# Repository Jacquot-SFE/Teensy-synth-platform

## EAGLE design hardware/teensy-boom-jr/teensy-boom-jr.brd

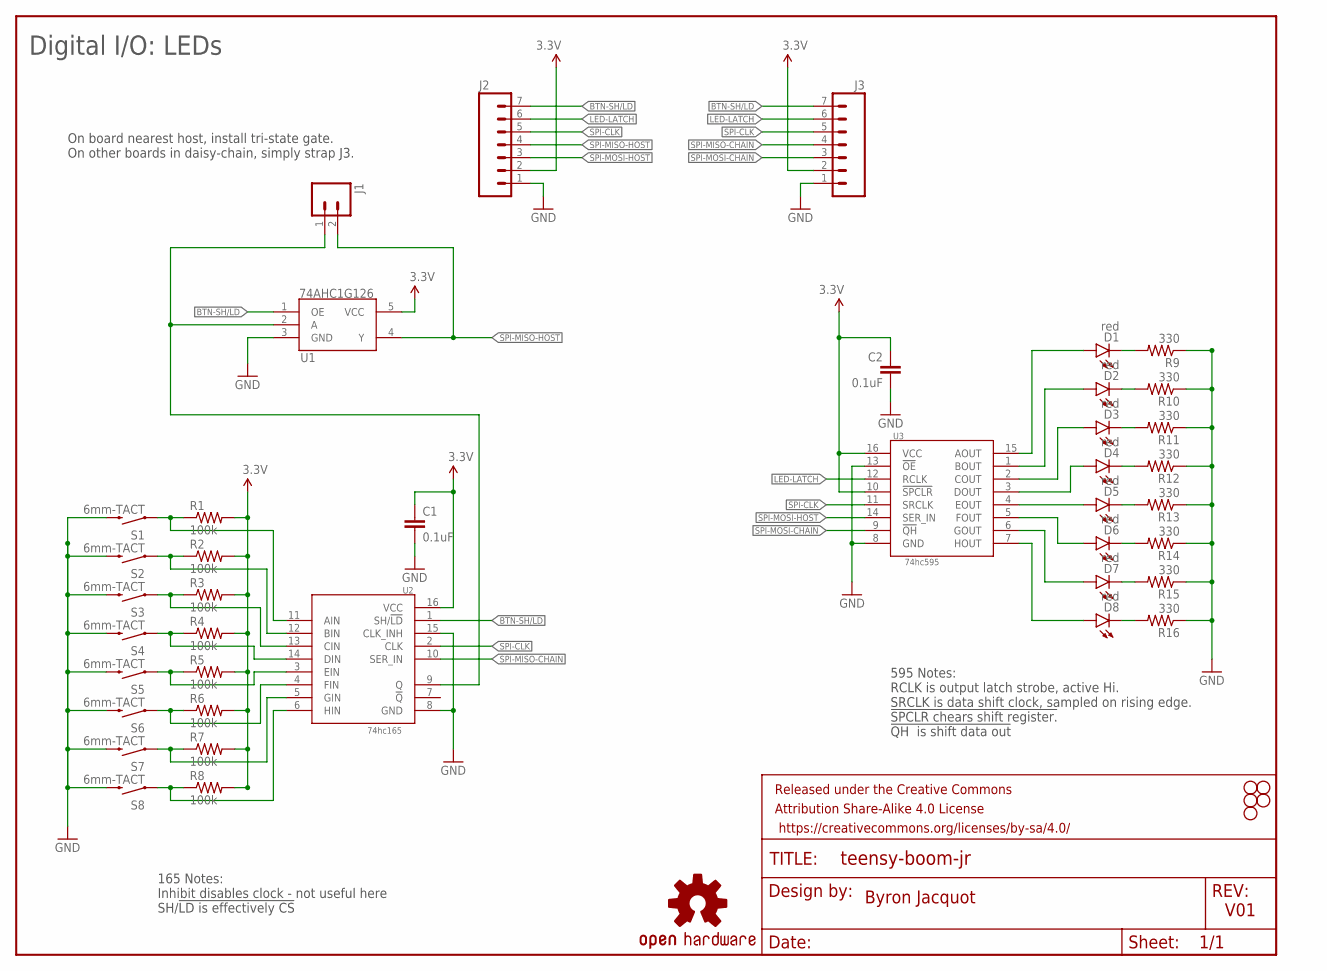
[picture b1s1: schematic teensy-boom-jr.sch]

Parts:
C1, C2: 0.1uF; 0603-CAP
D1, D2, D3, D4, D5, D6, D7, D8: red; LED3MM-NS
FRAME1: FRAME-LETTERNO_PACKAGE; DUMMY
H1, H2, H3, H4, H5: STAND-OFF
J1: M021X02_NO_SILK; 1X02_NO_SILK
J2, J3: M07NO_SILK; 1X07_NO_SILK
LOGO1: OSHW-LOGOS; OSHW-LOGO-S
R1, R2, R3, R4, R5, R6, R7, R8: 100k; 0805
R9, R10, R11, R12, R13, R14, R15, R16: 330; 0603-RES
S1, S2, S3, S4, S5, S6, S7, S8: 6mm-TACT; TACTILE-PTH-12MM
U1: 74AHC1G126; SOT23-5
U2: 74hc165; SO16
U3: 74hc595; SO16

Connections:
3.3V: C1.1, C2.1, J2.2, J3.2, R1.2, R2.2, R3.2, R4.2, R5.2, R6.2, R7.2, R8.2, U1.5 (VCC), U2.16 (VCC), U3.10 (!SPCLR), U3.16 (VCC)
BTN-SH/LD: J2.7, J3.7, U1.1 (OE), U2.1 (SH/!LD)
GND: C1.2, C2.2, J2.1, J3.1, R9.1, R10.1, R11.1, R12.1, R13.1, R14.1, R15.1, R16.1, S1.3 (2), S2.3 (2), S3.3 (2), S4.3 (2), S5.3 (2), S6.3 (2), S7.3 (2), S8.3 (2), U1.3 (GND), U2.8 (GND), U2.15 (CLK_INH), U3.8 (GND), U3.13 (!OE)
LED-LATCH: J2.6, J3.6, U3.12 (RCLK)
unnamed: R1.1, S1.1, U2.11 (AIN)
unnamed: R2.1, S2.1, U2.12 (BIN)
unnamed: R3.1, S3.1, U2.13 (CIN)
unnamed: R4.1, S4.1, U2.14 (DIN)
unnamed: D8.K (C), R16.2
unnamed: R5.1, S5.1, U2.3 (EIN)
unnamed: R6.1, S6.1, U2.4 (FIN)
unnamed: R7.1, S7.1, U2.5 (GIN)
unnamed: D7.K (C), R15.2
unnamed: D6.K (C), R14.2
unnamed: D5.K (C), R13.2
unnamed: D4.K (C), R12.2
unnamed: D3.K (C), R11.2
unnamed: D2.K (C), R10.2
unnamed: D1.K (C), R9.2
unnamed: R8.1, S8.1, U2.6 (HIN)
unnamed: J1.1, U1.2 (A), U2.9 (Q)
unnamed: D4.A, U3.3 (DOUT)
unnamed: D5.A, U3.4 (EOUT)
unnamed: D6.A, U3.5 (FOUT)
unnamed: D7.A, U3.6 (GOUT)
unnamed: D8.A, U3.7 (HOUT)
unnamed: D3.A, U3.2 (COUT)
unnamed: D2.A, U3.1 (BOUT)
unnamed: D1.A, U3.15 (AOUT)
SPI-CLK: J2.5, J3.5, U2.2 (CLK), U3.11 (SRCLK)
SPI-MISO-CHAIN: J3.4, U2.10 (SER_IN)
SPI-MISO-HOST: J1.2, J2.4, U1.4 (Y)
SPI-MOSI-CHAIN: J3.3, U3.9 (!QH)
SPI-MOSI-HOST: J2.3, U3.14 (SER_IN)

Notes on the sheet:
Digital I/O: LEDs
595 Notes: RCLK is output latch strobe, active Hi. SRCLK is data shift clock, sampled on rising edge. !SPCLR chears shift register. !QH is shift data out
On board nearest host, install tri-state gate. On other boards in daisy-chain, simply strap J3.
165 Notes: Inhibit disables clock - not useful here SH/!LD is effectively CS
Byron Jacquot
V01

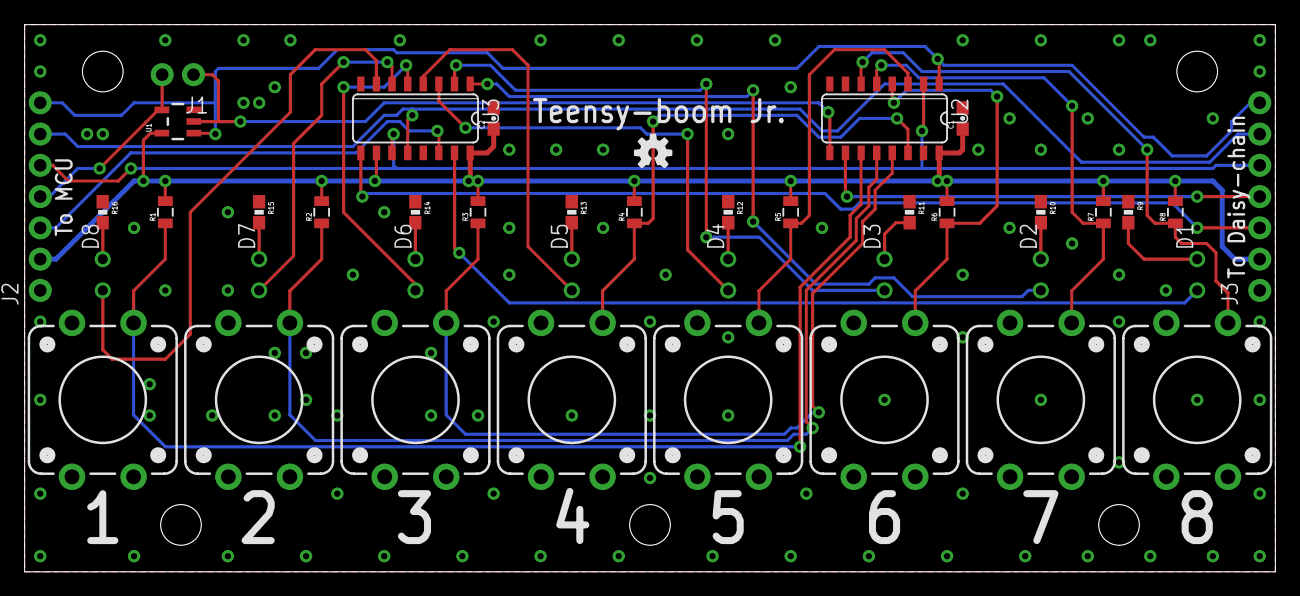
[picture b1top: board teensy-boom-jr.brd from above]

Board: 2 copper layers, 101.6 x 44.5 mm, 47 parts (0 on the bottom side), 34 nets.

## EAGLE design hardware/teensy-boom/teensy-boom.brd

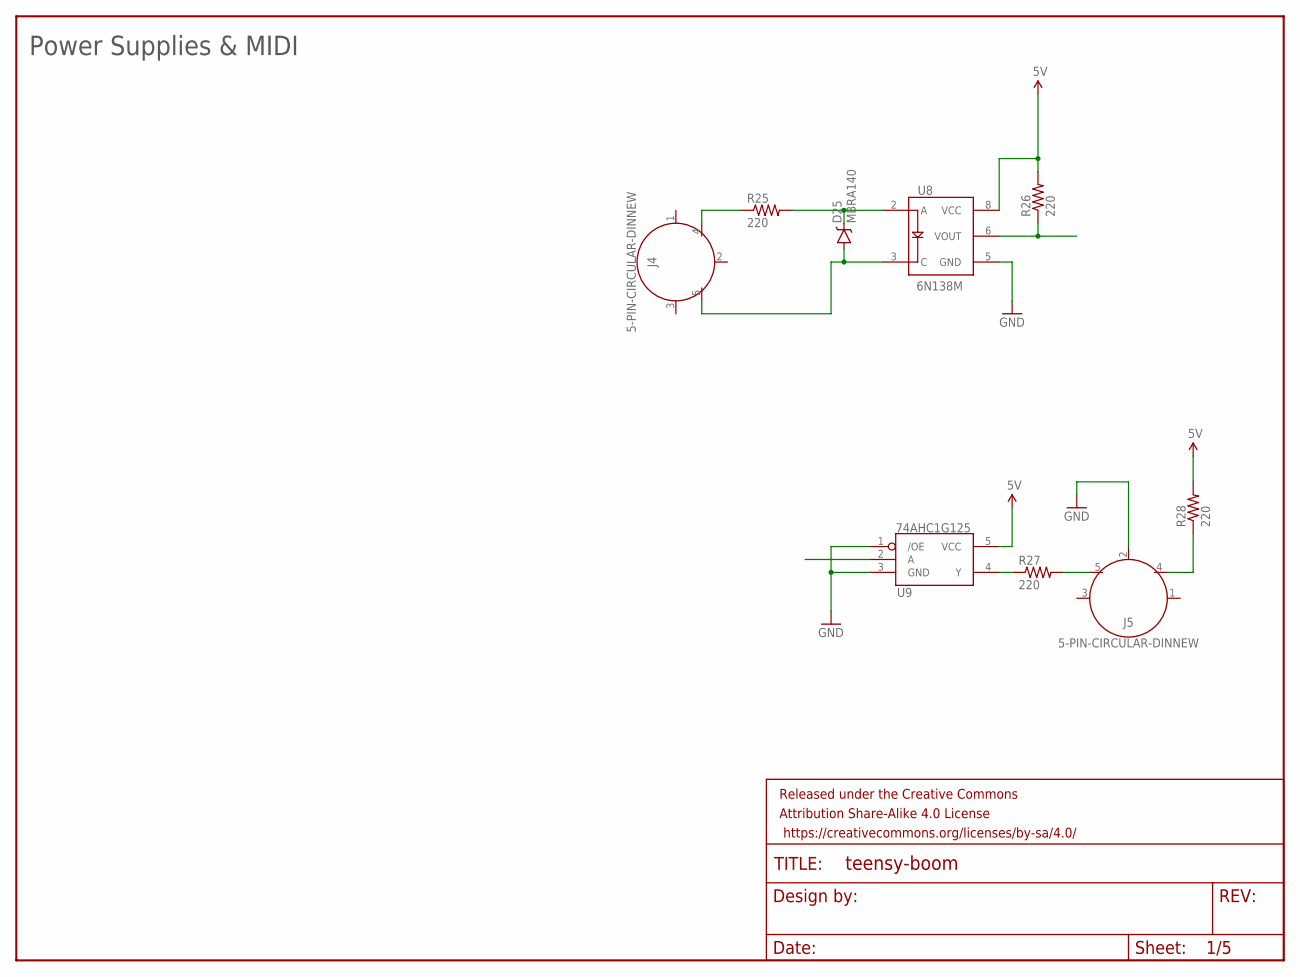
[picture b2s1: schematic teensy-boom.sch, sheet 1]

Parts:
D25: MBRA140; SMA-DIODE
FRAME2: FRAME-LETTERNO_PACKAGE; DUMMY
J4, J5: 5-PIN-CIRCULAR-DINNEW; 5-PIN-DIN-RA-PCB-NEW
R25, R26, R27, R28: 220; 0603-RES
U8: 6N138M; 8-SMD
U9: 74AHC1G125; SOT23-5

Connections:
5V: R26.2, R28.2, U8.8 (VCC), U9.5 (VCC)
GND: J5.2, U8.5 (GND), U9.1 (/OE), U9.3 (GND); also elsewhere on the board
unnamed: J4.4, R25.1
unnamed: D25.C, R25.2, U8.2 (A)
unnamed: D25.A, J4.5, U8.3 (C)
unnamed: R26.1, U8.6 (VOUT)
unnamed: R27.1, U9.4 (Y)
unnamed: J5.5, R27.2
unnamed: J5.4, R28.1

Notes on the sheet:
Power Supplies & MIDI

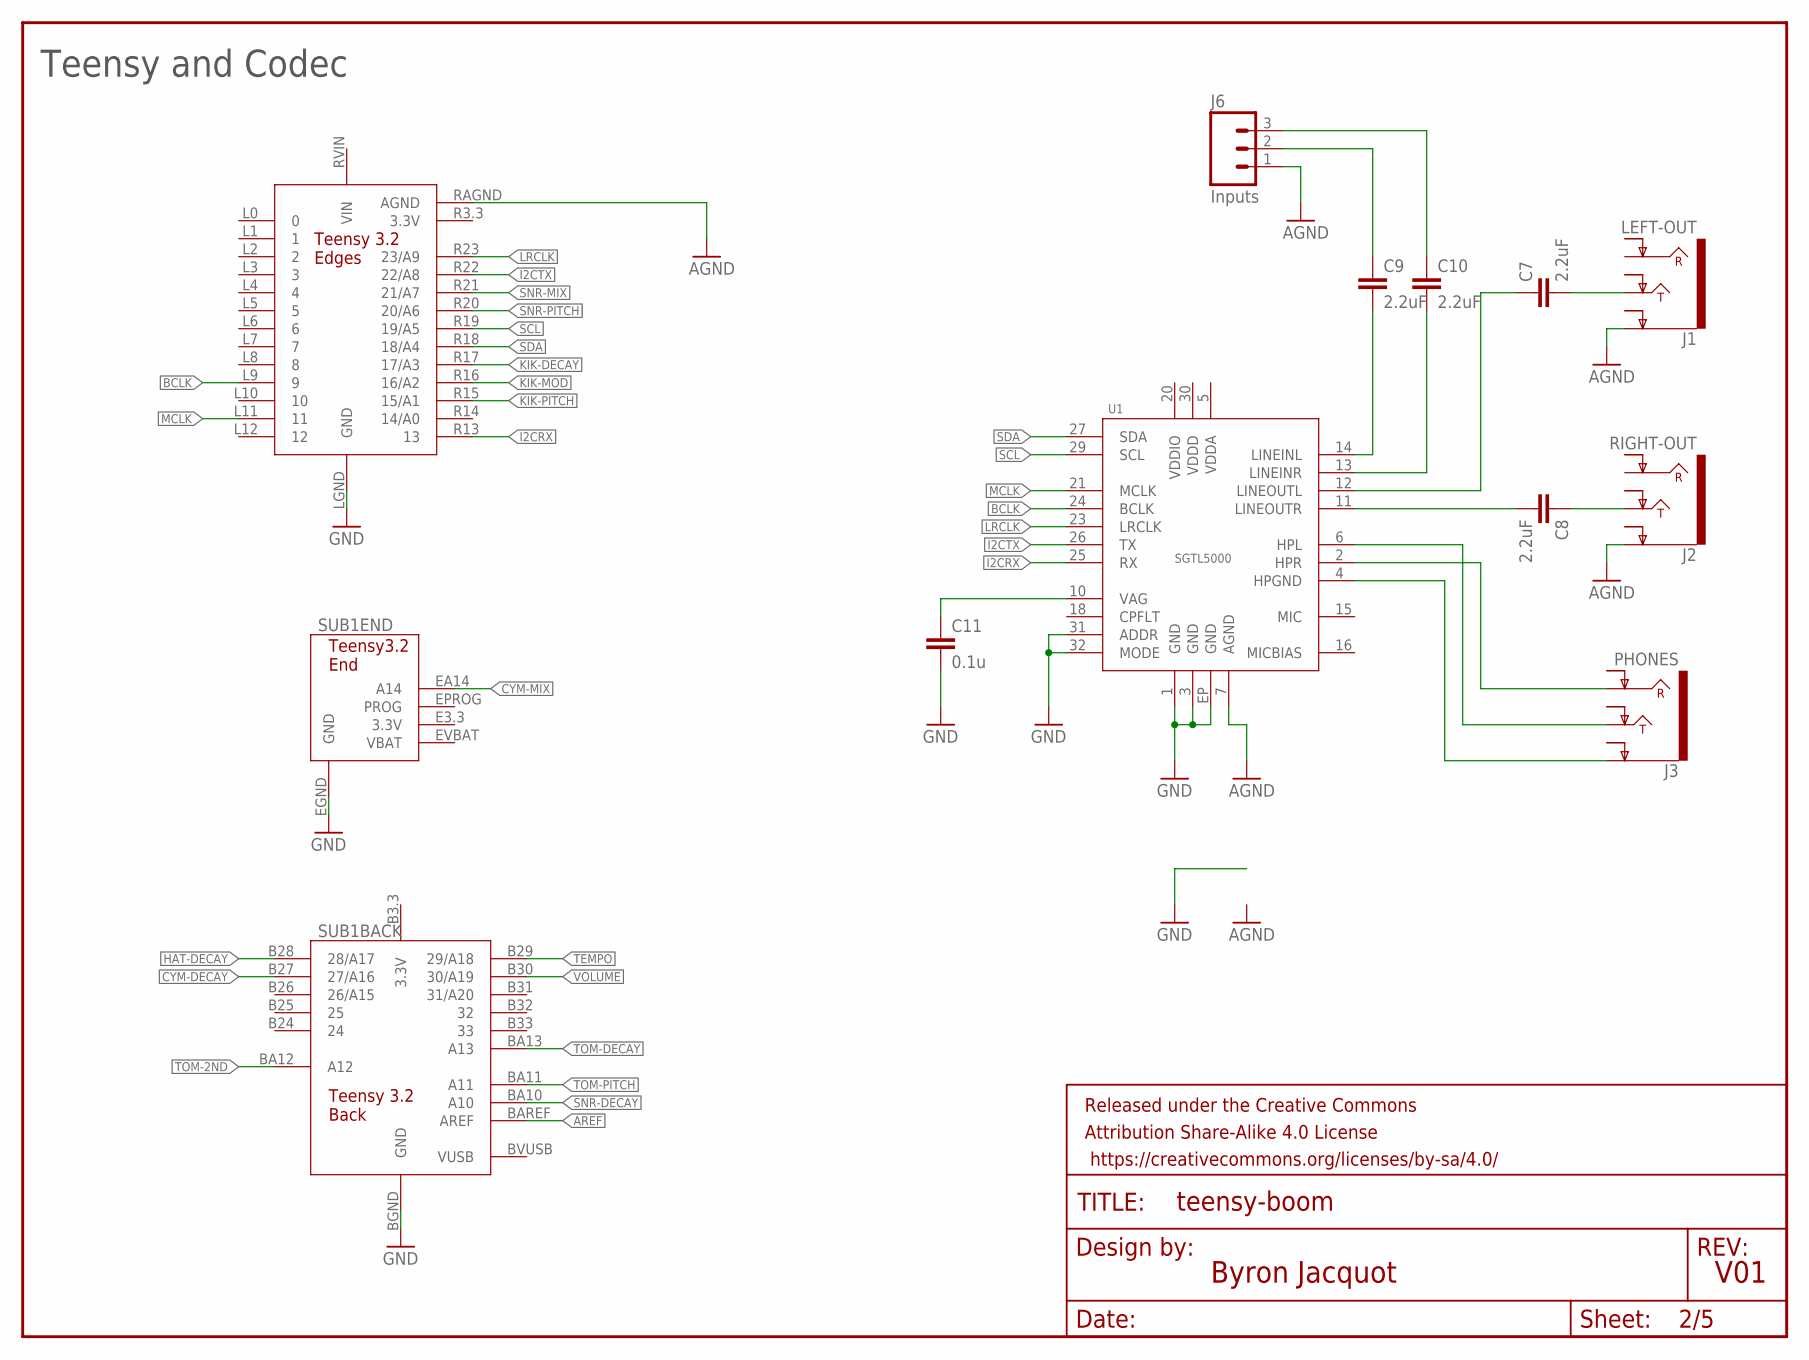
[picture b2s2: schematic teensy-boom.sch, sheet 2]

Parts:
C7, C8, C9, C10: 2.2uF; 0805-CAP
C11: 0.1u; 0805
FRAME1: FRAME-LETTER; CREATIVE_COMMONS
J1: LEFT-OUT; AUDIO-JACK-.25-INCH-HORIZ-PTH
J2: RIGHT-OUT; AUDIO-JACK-.25-INCH-HORIZ-PTH
J3: PHONES; AUDIO-JACK-.25-INCH-HORIZ-PTH
J6: Inputs; 1X03_LOCK
SUB1: TEENSY-3.2PTH; TEENSY-3.2
U1: SGTL5000; QFN-32

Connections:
AGND: J1.SLEEVE (EARTH), J2.SLEEVE (EARTH), J6.1, SUB1.RAGND (AGND), U1.7 (AGND); also elsewhere on the board
AREF: SUB1.BAREF (AREF); also elsewhere on the board
BCLK: SUB1.L9 (9), U1.24 (BCLK)
CYM-DECAY: SUB1.B27 (27/A16); also elsewhere on the board
CYM-MIX: SUB1.EA14 (A14); also elsewhere on the board
GND: C11.2, SUB1.BGND (GND), SUB1.EGND (GND), SUB1.LGND (GND), U1.1 (GND), U1.3 (GND), U1.31 (ADDR), U1.32 (MODE), U1.EP (GND); also elsewhere on the board
HAT-DECAY: SUB1.B28 (28/A17); also elsewhere on the board
I2CRX: SUB1.R13 (13), U1.25 (RX)
I2CTX: SUB1.R22 (22/A8), U1.26 (TX)
KIK-DECAY: SUB1.R17 (17/A3); also elsewhere on the board
KIK-MOD: SUB1.R16 (16/A2); also elsewhere on the board
KIK-PITCH: SUB1.R15 (15/A1); also elsewhere on the board
LRCLK: SUB1.R23 (23/A9), U1.23 (LRCLK)
MCLK: SUB1.L11 (11), U1.21 (MCLK)
unnamed: C8.1, J2.TIP
unnamed: C7.2, J1.TIP
unnamed: C8.2, U1.11 (LINEOUTR)
unnamed: C7.1, U1.12 (LINEOUTL)
unnamed: C10.2, U1.13 (LINEINR)
unnamed: C9.2, U1.14 (LINEINL)
unnamed: J3.TIP, U1.6 (HPL)
unnamed: J3.RING, U1.2 (HPR)
unnamed: J3.SLEEVE (EARTH), U1.4 (HPGND)
unnamed: C9.1, J6.2
unnamed: C10.1, J6.3
unnamed: C11.1, U1.10 (VAG)
SCL: SUB1.R19 (19/A5), U1.29 (SCL)
SDA: SUB1.R18 (18/A4), U1.27 (SDA)
SNR-DECAY: SUB1.BA10 (A10); also elsewhere on the board
SNR-MIX: SUB1.R21 (21/A7); also elsewhere on the board
SNR-PITCH: SUB1.R20 (20/A6); also elsewhere on the board
TEMPO: SUB1.B29 (29/A18); also elsewhere on the board
TOM-2ND: SUB1.BA12 (A12); also elsewhere on the board
TOM-DECAY: SUB1.BA13 (A13); also elsewhere on the board
TOM-PITCH: SUB1.BA11 (A11); also elsewhere on the board
VOLUME: SUB1.B30 (30/A19); also elsewhere on the board

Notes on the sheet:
V01
Byron Jacquot
Teensy and Codec

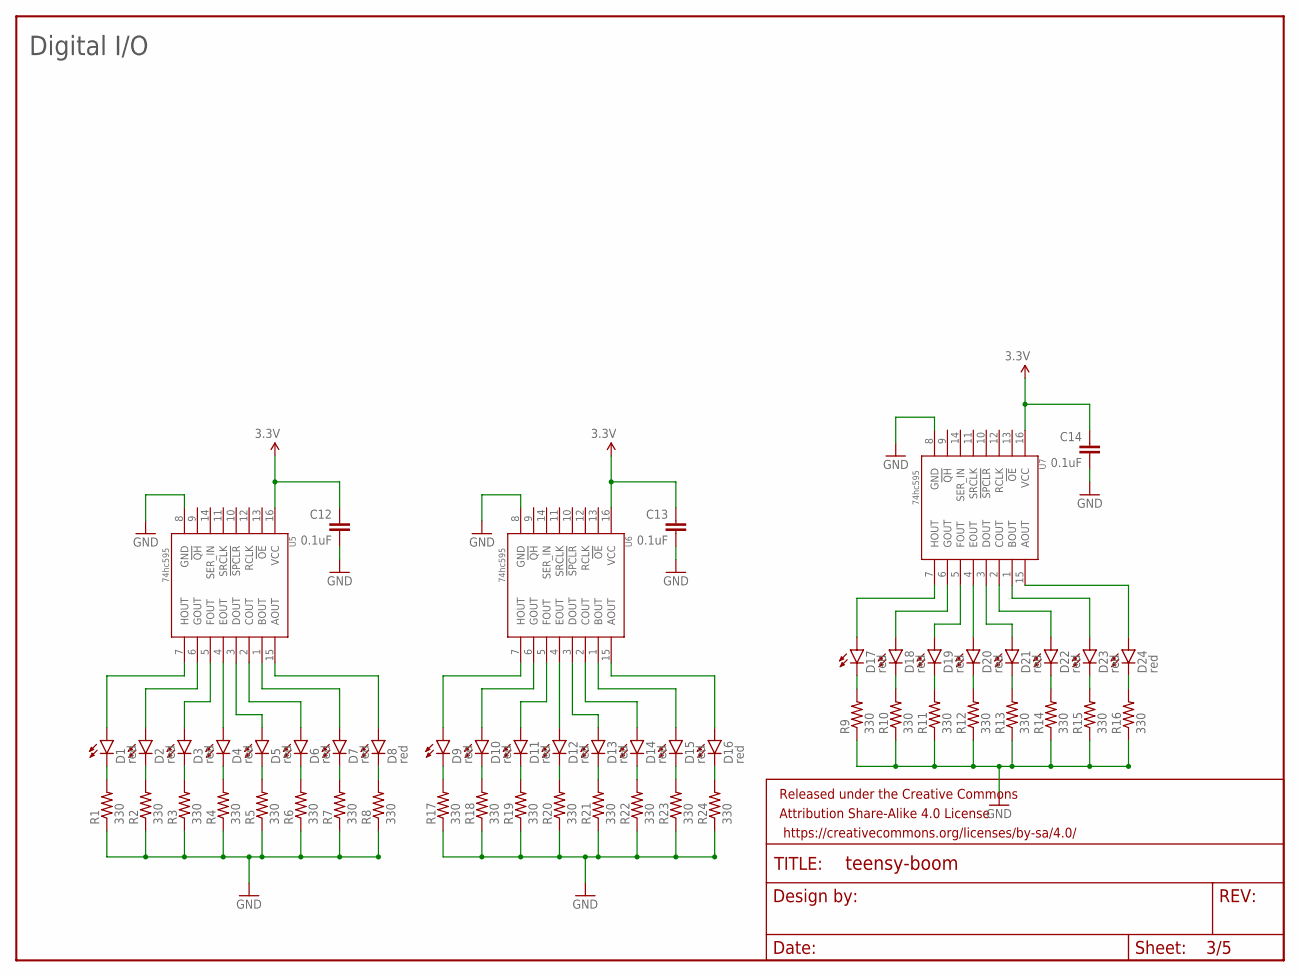
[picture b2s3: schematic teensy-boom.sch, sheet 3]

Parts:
C12, C13, C14: 0.1uF; 0603-CAP
D1, D2, D3, D4, D5, D6, D7, D8, D9, D10, D11, D12, D13, D14, D15, D16, D17, D18, D19, D20, D21, D22, D23, D24: red; LED3MM-NS
FRAME3: FRAME-LETTERNO_PACKAGE; DUMMY
R1, R2, R3, R4, R5, R6, R7, R8, R9, R10, R11, R12, R13, R14, R15, R16, R17, R18, R19, R20, R21, R22, R23, R24: 330; 0603-RES
U5, U6, U7: 74hc595; SO16

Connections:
3.3V: C12.1, C13.1, C14.1, U5.16 (VCC), U6.16 (VCC), U7.16 (VCC); also elsewhere on the board
GND: C12.2, C13.2, C14.2, R1.1, R2.1, R3.1, R4.1, R5.1, R6.1, R7.1, R8.1, R9.1, R10.1, R11.1, R12.1, R13.1, R14.1, R15.1, R16.1, R17.1, R18.1, R19.1, R20.1, R21.1, R22.1, R23.1, R24.1, U5.8 (GND), U6.8 (GND), U7.8 (GND); also elsewhere on the board
unnamed: D1.K (C), R1.2
unnamed: D2.K (C), R2.2
unnamed: D3.K (C), R3.2
unnamed: D4.K (C), R4.2
unnamed: D5.K (C), R5.2
unnamed: D6.K (C), R6.2
unnamed: D7.K (C), R7.2
unnamed: D8.K (C), R8.2
unnamed: D9.K (C), R17.2
unnamed: D10.K (C), R18.2
unnamed: D11.K (C), R19.2
unnamed: D12.K (C), R20.2
unnamed: D13.K (C), R21.2
unnamed: D14.K (C), R22.2
unnamed: D15.K (C), R23.2
unnamed: D16.K (C), R24.2
unnamed: D17.K (C), R9.2
unnamed: D18.K (C), R10.2
unnamed: D19.K (C), R11.2
unnamed: D20.K (C), R12.2
unnamed: D21.K (C), R13.2
unnamed: D22.K (C), R14.2
unnamed: D23.K (C), R15.2
unnamed: D24.K (C), R16.2
unnamed: D5.A, U5.3 (DOUT)
unnamed: D4.A, U5.4 (EOUT)
unnamed: D3.A, U5.5 (FOUT)
unnamed: D2.A, U5.6 (GOUT)
unnamed: D1.A, U5.7 (HOUT)
unnamed: D6.A, U5.2 (COUT)
unnamed: D7.A, U5.1 (BOUT)
unnamed: D8.A, U5.15 (AOUT)
unnamed: D12.A, U6.4 (EOUT)
unnamed: D11.A, U6.5 (FOUT)
unnamed: D10.A, U6.6 (GOUT)
unnamed: D9.A, U6.7 (HOUT)
unnamed: D13.A, U6.3 (DOUT)
unnamed: D14.A, U6.2 (COUT)
unnamed: D15.A, U6.1 (BOUT)
unnamed: D16.A, U6.15 (AOUT)
unnamed: D20.A, U7.4 (EOUT)
unnamed: D19.A, U7.5 (FOUT)
unnamed: D18.A, U7.6 (GOUT)
unnamed: D17.A, U7.7 (HOUT)
unnamed: D21.A, U7.3 (DOUT)
unnamed: D24.A, U7.15 (AOUT)
unnamed: D23.A, U7.1 (BOUT)
unnamed: D22.A, U7.2 (COUT)

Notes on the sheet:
Digital I/O

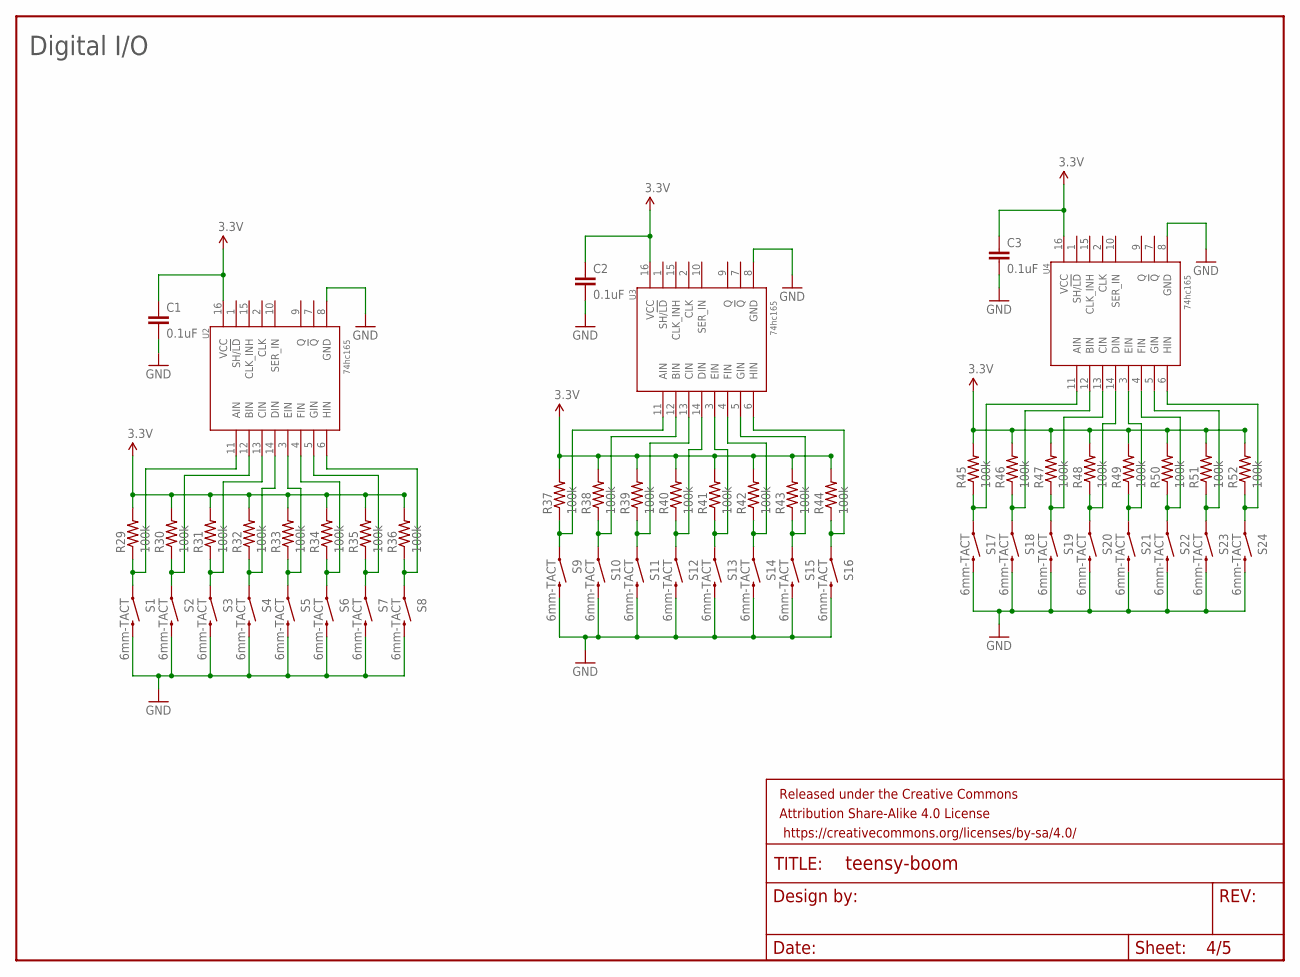
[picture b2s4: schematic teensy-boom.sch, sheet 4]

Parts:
C1, C2, C3: 0.1uF; 0603-CAP
FRAME5: FRAME-LETTERNO_PACKAGE; DUMMY
R29, R30, R31, R32, R33, R34, R35, R36, R37, R38, R39, R40, R41, R42, R43, R44, R45, R46, R47, R48, R49, R50, R51, R52: 100k; 0805
S1, S2, S3, S4, S5, S6, S7, S8, S9, S10, S11, S12, S13, S14, S15, S16, S17, S18, S19, S20, S21, S22, S23, S24: 6mm-TACT; TACTILE-PTH
U2, U3, U4: 74hc165; SO16

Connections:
3.3V: C1.1, C2.1, C3.1, R29.2, R30.2, R31.2, R32.2, R33.2, R34.2, R35.2, R36.2, R37.2, R38.2, R39.2, R40.2, R41.2, R42.2, R43.2, R44.2, R45.2, R46.2, R47.2, R48.2, R49.2, R50.2, R51.2, R52.2, U2.16 (VCC), U3.16 (VCC), U4.16 (VCC); also elsewhere on the board
GND: C1.2, C2.2, C3.2, S1.3 (2), S2.3 (2), S3.3 (2), S4.3 (2), S5.3 (2), S6.3 (2), S7.3 (2), S8.3 (2), S9.3 (2), S10.3 (2), S11.3 (2), S12.3 (2), S13.3 (2), S14.3 (2), S15.3 (2), S16.3 (2), S17.3 (2), S18.3 (2), S19.3 (2), S20.3 (2), S21.3 (2), S22.3 (2), S23.3 (2), S24.3 (2), U2.8 (GND), U3.8 (GND), U4.8 (GND); also elsewhere on the board
unnamed: R35.1, S7.1, U2.5 (GIN)
unnamed: R29.1, S1.1, U2.11 (AIN)
unnamed: R30.1, S2.1, U2.12 (BIN)
unnamed: R31.1, S3.1, U2.13 (CIN)
unnamed: R32.1, S4.1, U2.14 (DIN)
unnamed: R33.1, S5.1, U2.3 (EIN)
unnamed: R34.1, S6.1, U2.4 (FIN)
unnamed: R36.1, S8.1, U2.6 (HIN)
unnamed: R37.1, S9.1, U3.11 (AIN)
unnamed: R38.1, S10.1, U3.12 (BIN)
unnamed: R39.1, S11.1, U3.13 (CIN)
unnamed: R40.1, S12.1, U3.14 (DIN)
unnamed: R41.1, S13.1, U3.3 (EIN)
unnamed: R42.1, S14.1, U3.4 (FIN)
unnamed: R43.1, S15.1, U3.5 (GIN)
unnamed: R44.1, S16.1, U3.6 (HIN)
unnamed: R45.1, S17.1, U4.11 (AIN)
unnamed: R46.1, S18.1, U4.12 (BIN)
unnamed: R47.1, S19.1, U4.13 (CIN)
unnamed: R48.1, S20.1, U4.14 (DIN)
unnamed: R49.1, S21.1, U4.3 (EIN)
unnamed: R50.1, S22.1, U4.4 (FIN)
unnamed: R51.1, S23.1, U4.5 (GIN)
unnamed: R52.1, S24.1, U4.6 (HIN)

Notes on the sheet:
Digital I/O

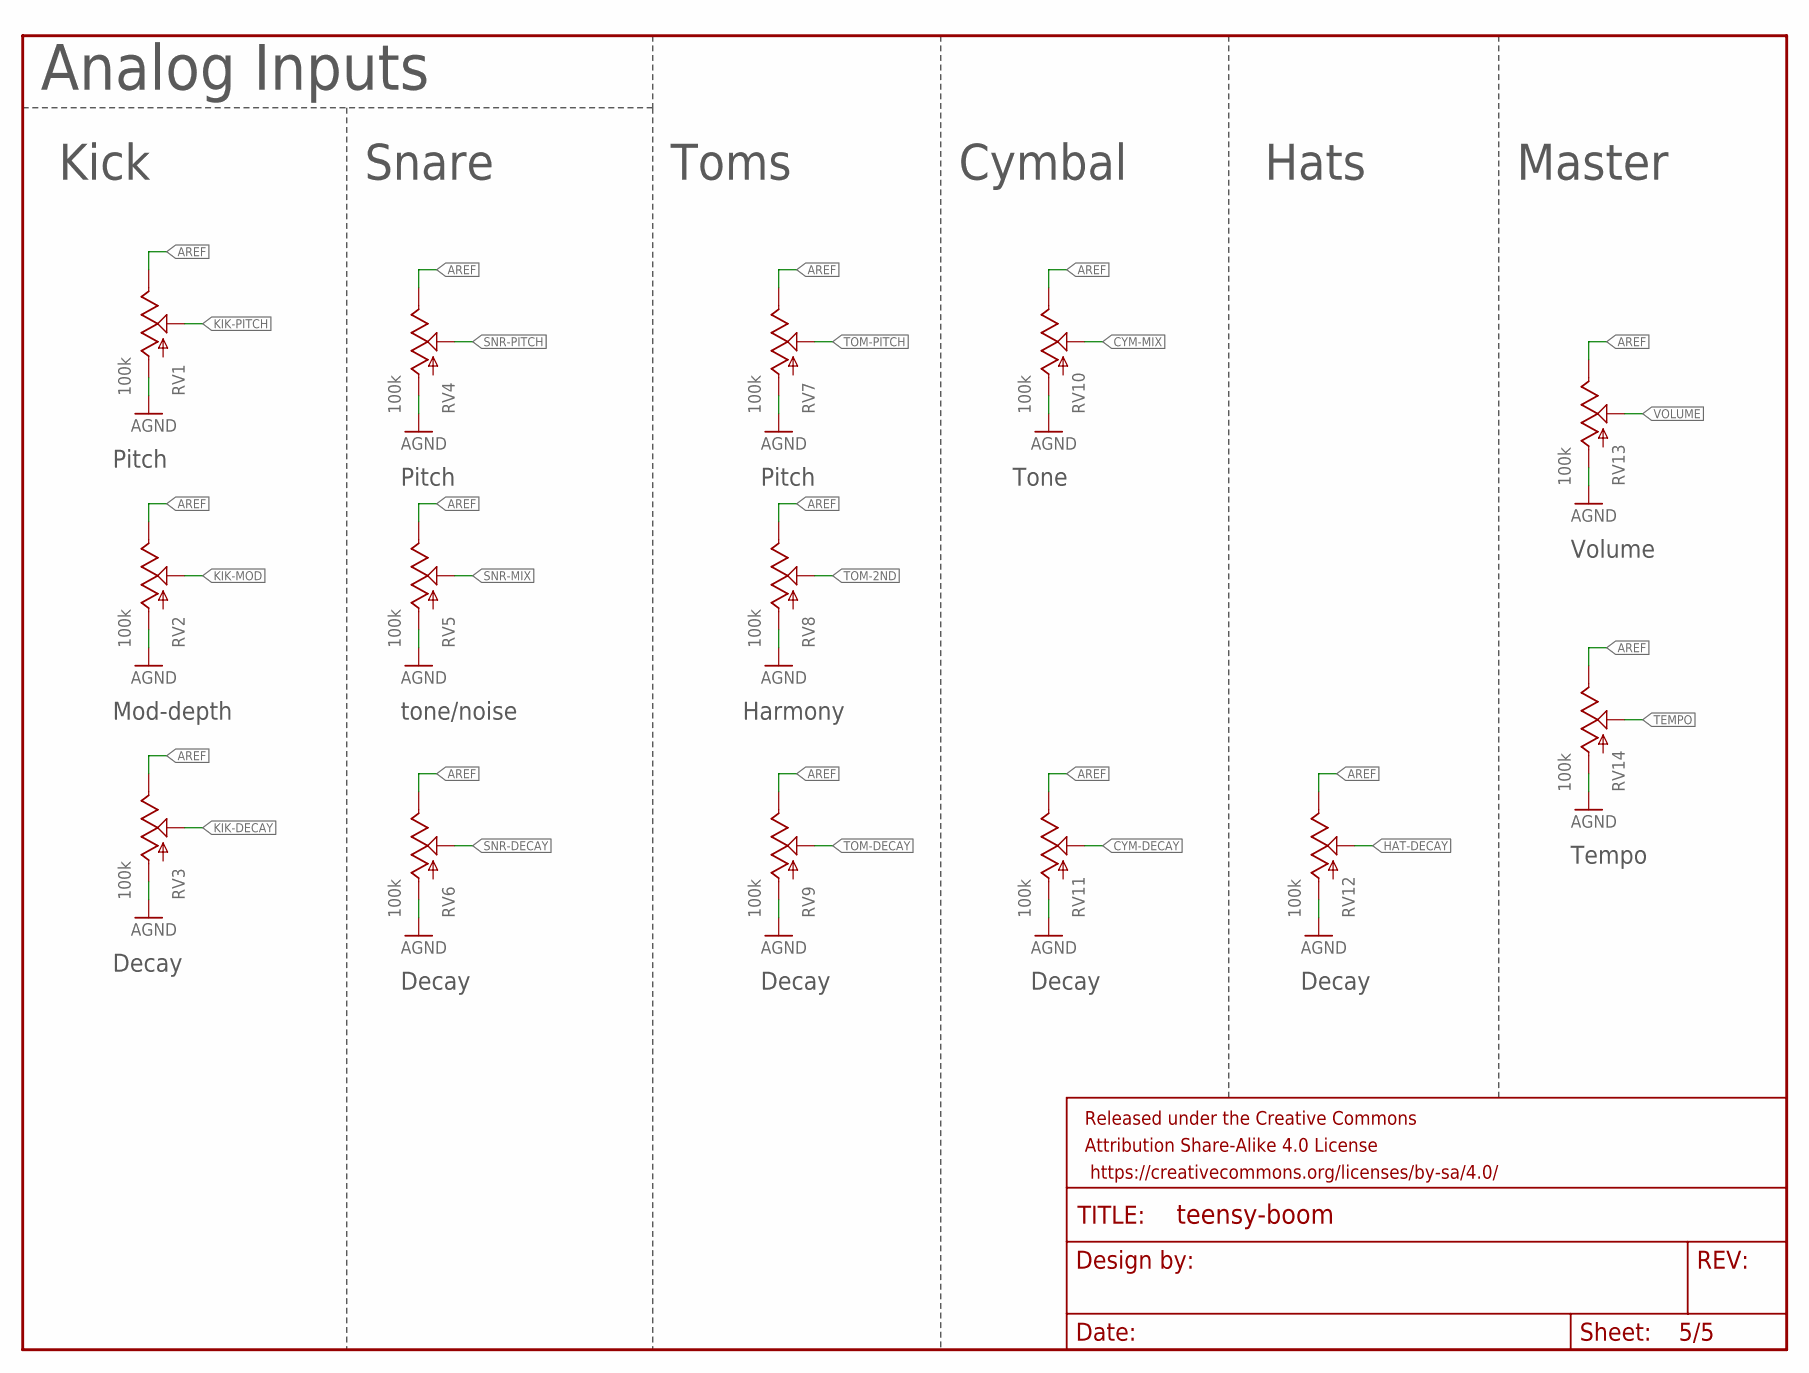
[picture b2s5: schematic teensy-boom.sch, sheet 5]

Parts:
FRAME4: FRAME-LETTERNO_PACKAGE; DUMMY
RV1, RV2, RV3, RV4, RV5, RV6, RV7, RV8, RV9, RV10, RV11, RV12, RV13, RV14: 100k; ALPS_POT_KIT

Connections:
AGND: RV1.P$3 (A), RV2.P$3 (A), RV3.P$3 (A), RV4.P$3 (A), RV5.P$3 (A), RV6.P$3 (A), RV7.P$3 (A), RV8.P$3 (A), RV9.P$3 (A), RV10.P$3 (A), RV11.P$3 (A), RV12.P$3 (A), RV13.P$3 (A), RV14.P$3 (A); also elsewhere on the board
AREF: RV1.P$1 (E), RV2.P$1 (E), RV3.P$1 (E), RV4.P$1 (E), RV5.P$1 (E), RV6.P$1 (E), RV7.P$1 (E), RV8.P$1 (E), RV9.P$1 (E), RV10.P$1 (E), RV11.P$1 (E), RV12.P$1 (E), RV13.P$1 (E), RV14.P$1 (E); also elsewhere on the board
CYM-DECAY: RV11.P$2 (S); also elsewhere on the board
CYM-MIX: RV10.P$2 (S); also elsewhere on the board
HAT-DECAY: RV12.P$2 (S); also elsewhere on the board
KIK-DECAY: RV3.P$2 (S); also elsewhere on the board
KIK-MOD: RV2.P$2 (S); also elsewhere on the board
KIK-PITCH: RV1.P$2 (S); also elsewhere on the board
SNR-DECAY: RV6.P$2 (S); also elsewhere on the board
SNR-MIX: RV5.P$2 (S); also elsewhere on the board
SNR-PITCH: RV4.P$2 (S); also elsewhere on the board
TEMPO: RV14.P$2 (S); also elsewhere on the board
TOM-2ND: RV8.P$2 (S); also elsewhere on the board
TOM-DECAY: RV9.P$2 (S); also elsewhere on the board
TOM-PITCH: RV7.P$2 (S); also elsewhere on the board
VOLUME: RV13.P$2 (S); also elsewhere on the board

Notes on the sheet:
Analog Inputs
Tempo
Volume
Pitch
Mod-depth
Decay
tone/noise
Harmony
Tone
Kick
Snare
Toms
Cymbal
Hats
Master

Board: 2 copper layers, 147 parts (56 on the bottom side), 117 nets, no tracks yet.

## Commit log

2015-12-09 :tada: Added .gitattributes & .gitignore files
2015-12-09 Adding a first stab at docs.
2015-12-09 Added Form Factor bullet
2015-12-11 added some multiplexing research
2015-12-11 did some power supply research
2015-12-14 added basic transformer simulation
2015-12-14 Added discrete flyback simulation
2015-12-14 deleted lock
2015-12-16 Added decode summer to options and topology
2015-12-18 updated topology and created kicad project
2015-12-19 worked on layout
2015-12-28 Adding concept spec for Teensy-boom
2015-12-28 Some small updates, seeing the MD rendered for real
2015-12-30 Testing out new dual trimpot footprint
2016-01-03 removed kicad project
2016-01-09 Getting more complete .gitignore
2016-01-09 Another update to .gitignore, and boom initial files.
2016-01-09 Adding sgtl5000 to library.
    Need to doublecheck the TX/RX pins. Is the terminilogy always in
    reference to the bus master?
2016-01-12 More PCB work
    Added knobs, buttons, connectors, MIDI.
    Basic PCB alignment in place...~6"x4"
2016-01-19 More work on PCB/Schem
2016-01-21 More work on BOOM schem/PCB.
2016-01-26 updated docs
2016-02-08 Checking in WIP of large Teensy-BOOM board, so I can move to smaller one.
2016-02-10 Adding teensy-boom Junior board.
2016-02-10 Small updates to get ready to fab.
2016-02-21 Added FreeCAD parts for first cheeks
2016-02-21 generated toolpaths
2016-02-21 adjusted margins
2016-02-22 photographed the testbed
2016-02-26 Starting presentation slide deck.
2016-02-26 Slide updates.
2016-02-29 Small slide updates
    Making sure the presentation runs on my laptop.
2016-03-02 worked on documentation
2016-03-03 Bunch of updates to slide deck.
2016-03-03 Added HW details
2016-03-04 One last touchup to slide deck.
2016-03-04 moved images

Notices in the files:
parts and their libraries:
SparkFun-Aesthetics: Licensing: Creative Commons ShareAlike 4.0 International - https://creativecommons.org/licenses/by-sa/4.0
SparkFun-Aesthetics: Released under the Creative Commons Attribution Share-Alike 4.0 License
SparkFun-Aesthetics: https://creativecommons.org/licenses/by-sa/4.0
